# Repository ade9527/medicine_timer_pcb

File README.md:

# Medicine timer hardware

pcb is built using kicad.

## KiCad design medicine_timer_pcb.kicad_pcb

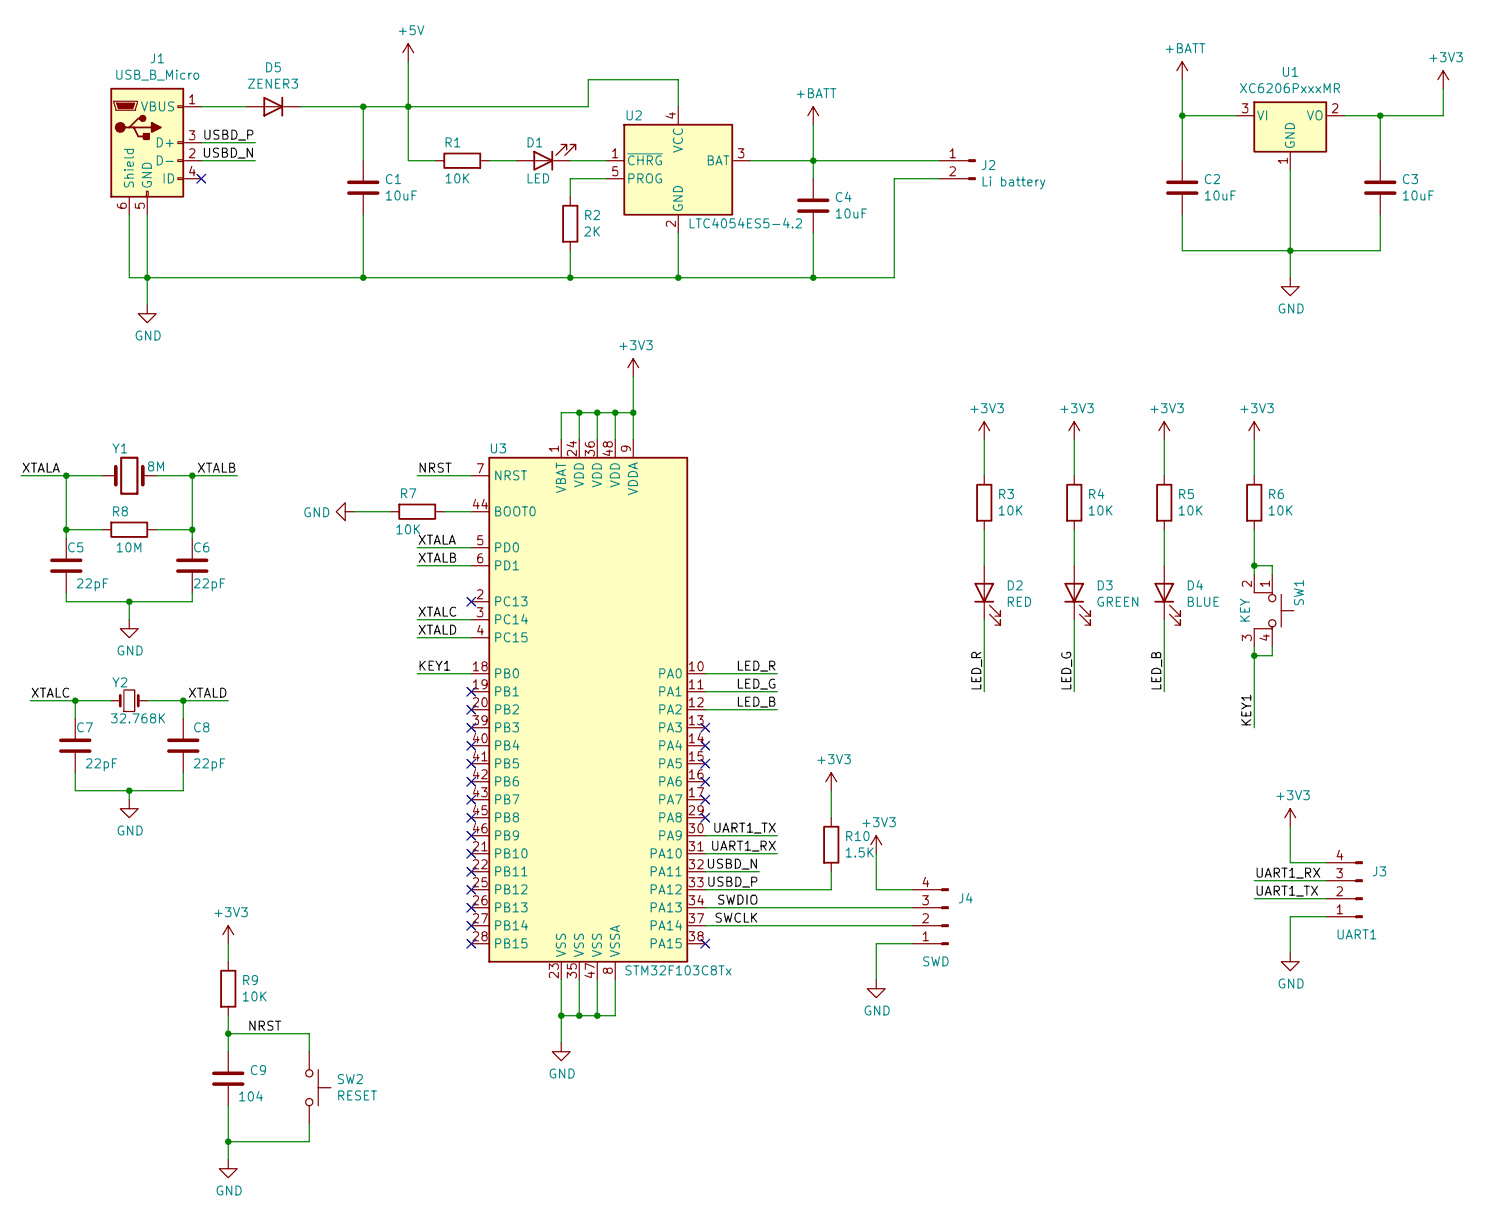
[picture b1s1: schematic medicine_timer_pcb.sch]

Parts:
C1, C2, C3, C4: 10uF; C_0603_1608Metric
C5, C6, C7, C8: 22pF; C_0603_1608Metric
C9: 104; C_0603_1608Metric
D1: LED; LED_0603_1608Metric
D2: RED; LED_0603_1608Metric
D3: GREEN; LED_0603_1608Metric
D4: BLUE; LED_0603_1608Metric
D5: ZENER3; D_SOD-123
J1: USB_B_Micro; USB_Micro-B_Molex_47346-0001
J2: Li battery; SOIC-2
J3: UART1; PinHeader_1x04_P2.00mm_Vertical
J4: SWD; PinHeader_1x04_P2.00mm_Vertical
R1, R3, R4, R5, R6, R7, R9: 10K; R_0603_1608Metric
R2: 2K; R_0603_1608Metric
R8: 10M; R_0603_1608Metric
R10: 1.5K; R_0603_1608Metric
SW1: KEY; SW_SPST_Omron_B3FS-100xP
SW2: RESET; SW_SPST_FSMSM
U1: XC6206PxxxMR; SOT-23
U2: LTC4054ES5-4.2; TSOT-23-5
U3: STM32F103C8Tx; LQFP-48_7x7mm_P0.5mm
Y1: 8M; Crystal_SMD_SeikoEpson_MA505-2Pin_12.7x5.1mm
Y2: 32.768K; Crystal_SMD_3215-2Pin_3.2x1.5mm

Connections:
+3V3: C3.1, J3.4, J4.4, R3.1, R4.1, R5.1, R6.1, R9.1, R10.1, U1.2 (VO), U3.1 (VBAT), U3.9 (VDDA), U3.24 (VDD), U3.36 (VDD), U3.48 (VDD)
+5V: C1.1, D5.1 (K), R1.1, U2.4 (VCC)
+BATT: C2.1, C4.1, J2.1, U1.3 (VI), U2.3 (BAT)
/KEY1: SW1.3 (K), SW1.4 (A), U3.18 (PB0)
/LED_B: D4.1 (K), U3.12 (PA2)
/LED_G: D3.1 (K), U3.11 (PA1)
/LED_R: D2.1 (K), U3.10 (PA0)
/NRST: C9.1, R9.2, SW2.1, U3.7 (NRST)
/SWCLK: J4.2, U3.37 (PA14)
/SWDIO: J4.3, U3.34 (PA13)
/UART1_RX: J3.3, U3.31 (PA10)
/UART1_TX: J3.2, U3.30 (PA9)
/USBD_N: J1.2 (D-), U3.32 (PA11)
/USBD_P: J1.3 (D+), R10.2, U3.33 (PA12)
/XTALA: C5.1, R8.2, U3.5 (PD0), Y1.2
/XTALB: C6.1, R8.1, U3.6 (PD1), Y1.1
/XTALC: C7.1, U3.3 (PC14), Y2.1
/XTALD: C8.1, U3.4 (PC15), Y2.2
GND: C1.2, C2.2, C3.2, C4.2, C5.2, C6.2, C7.2, C8.2, C9.2, J1.5 (GND), J1.6 (Shield), J2.2, J3.1, J4.1, R2.2, R7.2, SW2.2, U1.1 (GND), U2.2 (GND), U3.8 (VSSA), U3.23 (VSS), U3.35 (VSS), U3.47 (VSS)
unnamed: D1.1 (K), U2.1 (~CHRG)
unnamed: D1.2 (A), R1.2
unnamed: D2.2 (A), R3.2
unnamed: D3.2 (A), R4.2
unnamed: D4.2 (A), R5.2
unnamed: D5.2 (A), J1.1 (VBUS)
unnamed: R2.1, U2.5 (PROG)
unnamed: R6.2, SW1.1, SW1.2
unnamed: R7.1, U3.44 (BOOT0)

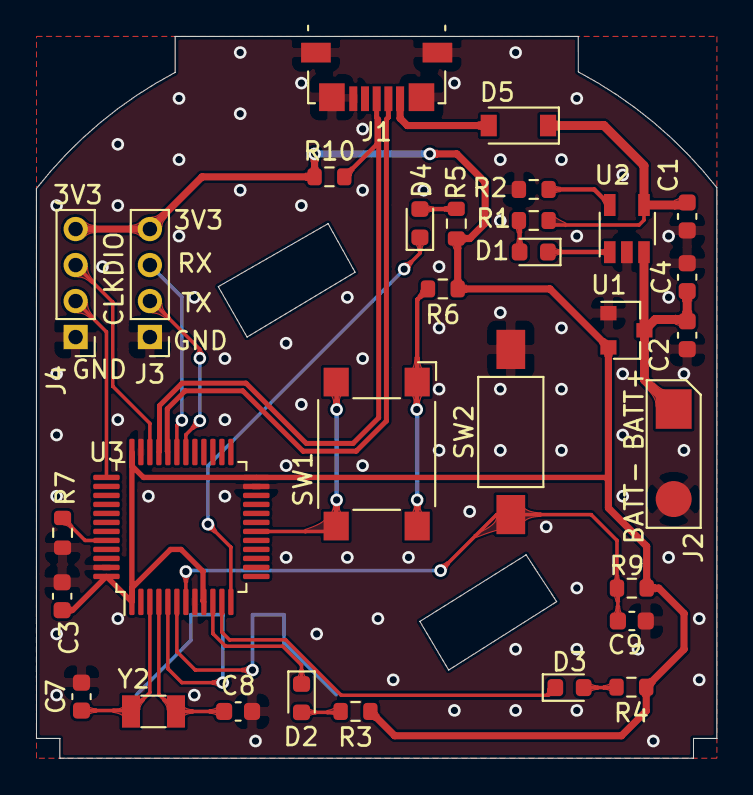
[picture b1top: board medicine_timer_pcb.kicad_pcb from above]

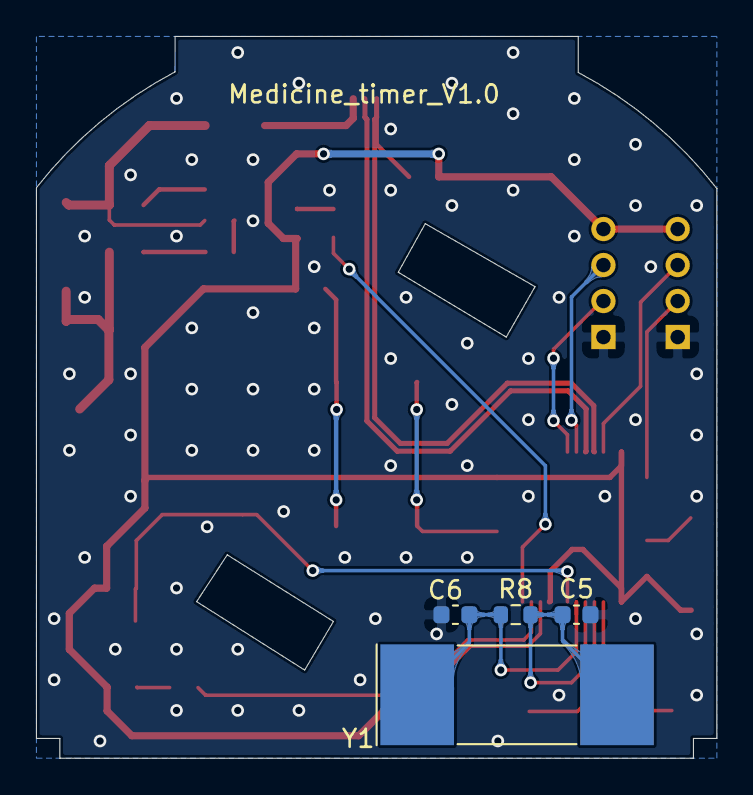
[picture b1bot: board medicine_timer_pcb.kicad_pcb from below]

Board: 2 copper layers, 37.8 x 40.1 mm, 35 parts (4 on the bottom side), 28 nets.

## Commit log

2021-01-26 First commit,add PCB file.
